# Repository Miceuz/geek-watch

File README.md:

# geek-watch
My take on building a watch.

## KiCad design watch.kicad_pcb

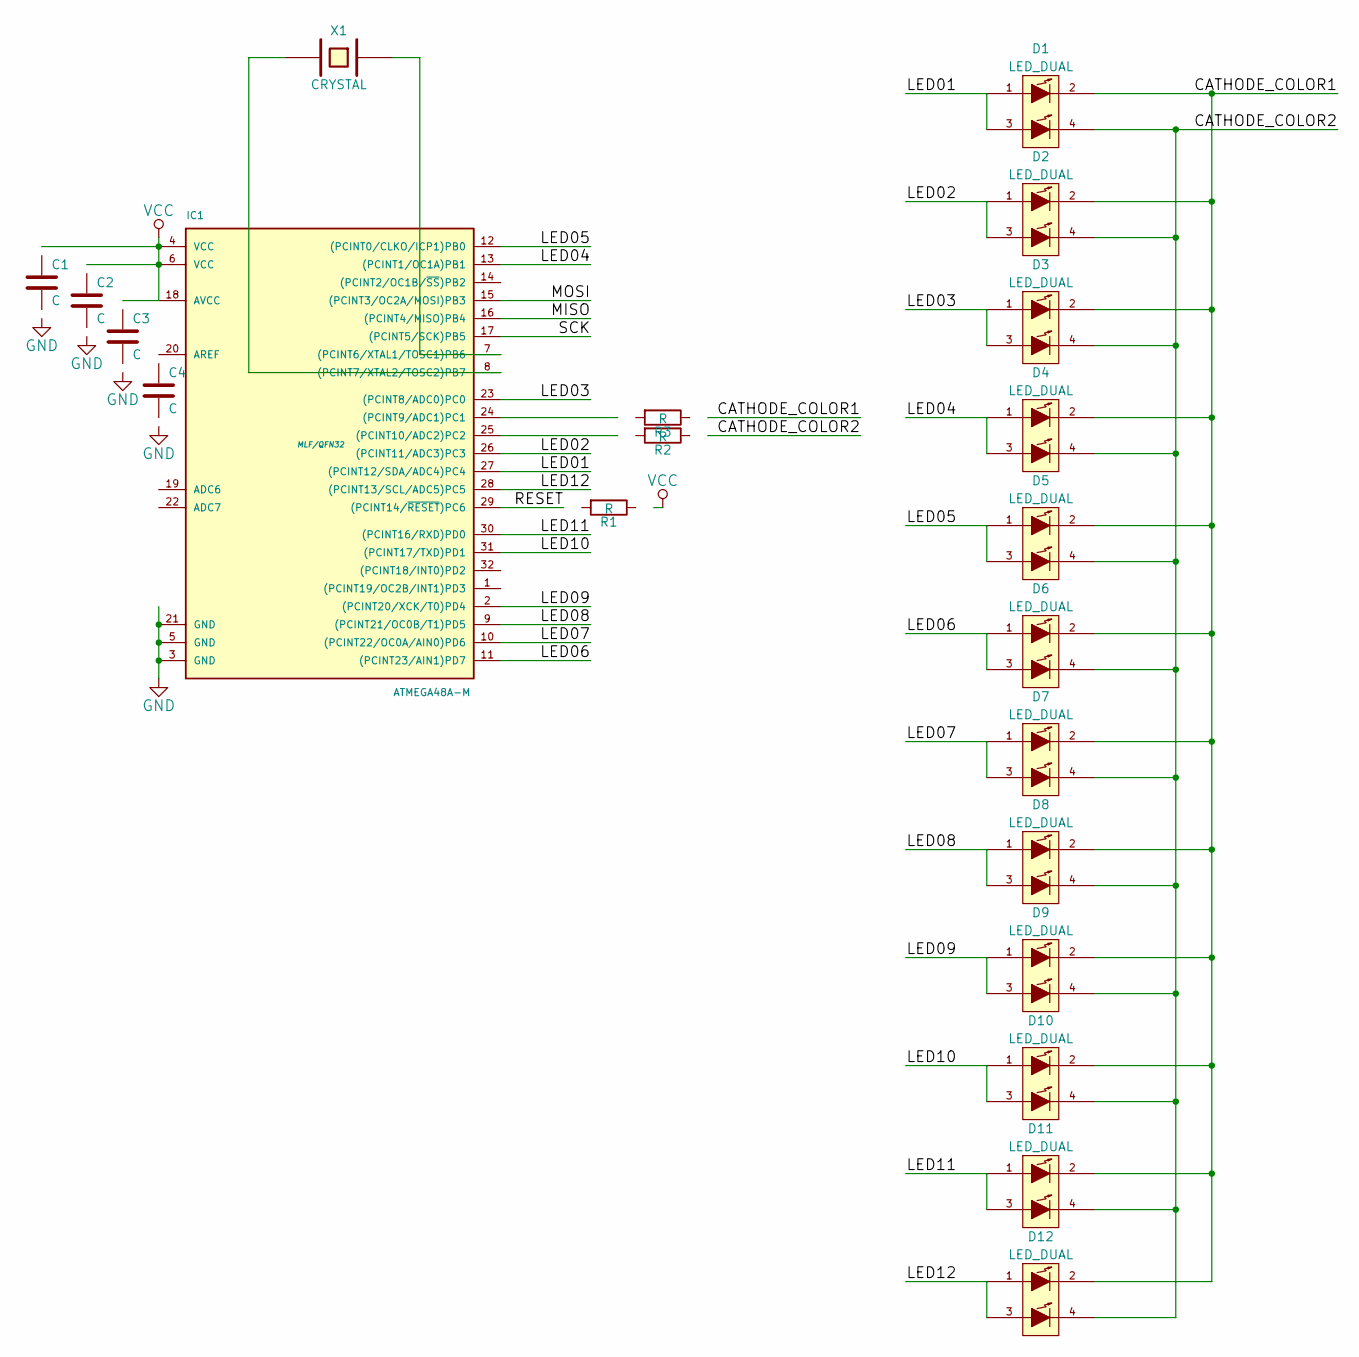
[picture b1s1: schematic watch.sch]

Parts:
C1, C2, C3, C4: C
D1, D2, D3, D4, D5, D6, D7, D8, D9, D10, D11, D12: LED_DUAL
IC1: ATMEGA48A-M; MLF/QFN32
R1, R2, R3: R
X1: CRYSTAL

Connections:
/CATHODE_COLOR1: D1.2 (RED_CATHODE), D2.2 (RED_CATHODE), D3.2 (RED_CATHODE), D4.2 (RED_CATHODE), D5.2 (RED_CATHODE), D6.2 (RED_CATHODE), D7.2 (RED_CATHODE), D8.2 (RED_CATHODE), D9.2 (RED_CATHODE), D10.2 (RED_CATHODE), D11.2 (RED_CATHODE), D12.2 (RED_CATHODE), R3.1
/CATHODE_COLOR2: D1.4 (GREEN_CATHODE), D2.4 (GREEN_CATHODE), D3.4 (GREEN_CATHODE), D4.4 (GREEN_CATHODE), D5.4 (GREEN_CATHODE), D6.4 (GREEN_CATHODE), D7.4 (GREEN_CATHODE), D8.4 (GREEN_CATHODE), D9.4 (GREEN_CATHODE), D10.4 (GREEN_CATHODE), D11.4 (GREEN_CATHODE), D12.4 (GREEN_CATHODE), R2.1
/LED01: D1.1 (RED_ANODE), D1.3 (GREEN_ANODE), IC1.27 ((PCINT12/SDA/ADC4)PC4)
/LED02: D2.1 (RED_ANODE), D2.3 (GREEN_ANODE), IC1.26 ((PCINT11/ADC3)PC3)
/LED03: D3.1 (RED_ANODE), D3.3 (GREEN_ANODE), IC1.23 ((PCINT8/ADC0)PC0)
/LED04: D4.1 (RED_ANODE), D4.3 (GREEN_ANODE), IC1.13 ((PCINT1/OC1A)PB1)
/LED05: D5.1 (RED_ANODE), D5.3 (GREEN_ANODE), IC1.12 ((PCINT0/CLKO/ICP1)PB0)
/LED06: D6.1 (RED_ANODE), D6.3 (GREEN_ANODE), IC1.11 ((PCINT23/AIN1)PD7)
/LED07: D7.1 (RED_ANODE), D7.3 (GREEN_ANODE), IC1.10 ((PCINT22/OC0A/AIN0)PD6)
/LED08: D8.1 (RED_ANODE), D8.3 (GREEN_ANODE), IC1.9 ((PCINT21/OC0B/T1)PD5)
/LED09: D9.1 (RED_ANODE), D9.3 (GREEN_ANODE), IC1.2 ((PCINT20/XCK/T0)PD4)
/LED10: D10.1 (RED_ANODE), D10.3 (GREEN_ANODE), IC1.31 ((PCINT17/TXD)PD1)
/LED11: D11.1 (RED_ANODE), D11.3 (GREEN_ANODE), IC1.30 ((PCINT16/RXD)PD0)
/LED12: D12.1 (RED_ANODE), D12.3 (GREEN_ANODE), IC1.28 ((PCINT13/SCL/ADC5)PC5)
/MISO: IC1.16 ((PCINT4/MISO)PB4); also elsewhere on the board
/MOSI: IC1.15 ((PCINT3/OC2A/MOSI)PB3); also elsewhere on the board
/RESET: IC1.29 ((PCINT14/~RESET~)PC6), R1.2; also elsewhere on the board
/SCK: IC1.17 ((PCINT5/SCK)PB5); also elsewhere on the board
GND: C1.2, C2.2, C3.2, IC1.3 (GND), IC1.5 (GND), IC1.21 (GND), IC1.33; also elsewhere on the board
unnamed: IC1.7 ((PCINT6/XTAL1/TOSC1)PB6), X1.1
unnamed: IC1.8 ((PCINT7/XTAL2/TOSC2)PB7), X1.2
unnamed: IC1.24 ((PCINT9/ADC1)PC1), R3.2
unnamed: IC1.25 ((PCINT10/ADC2)PC2), R2.2
VCC: C1.1, C2.1, C3.1, IC1.4 (VCC), IC1.6 (VCC), IC1.18 (AVCC), R1.1; also elsewhere on the board

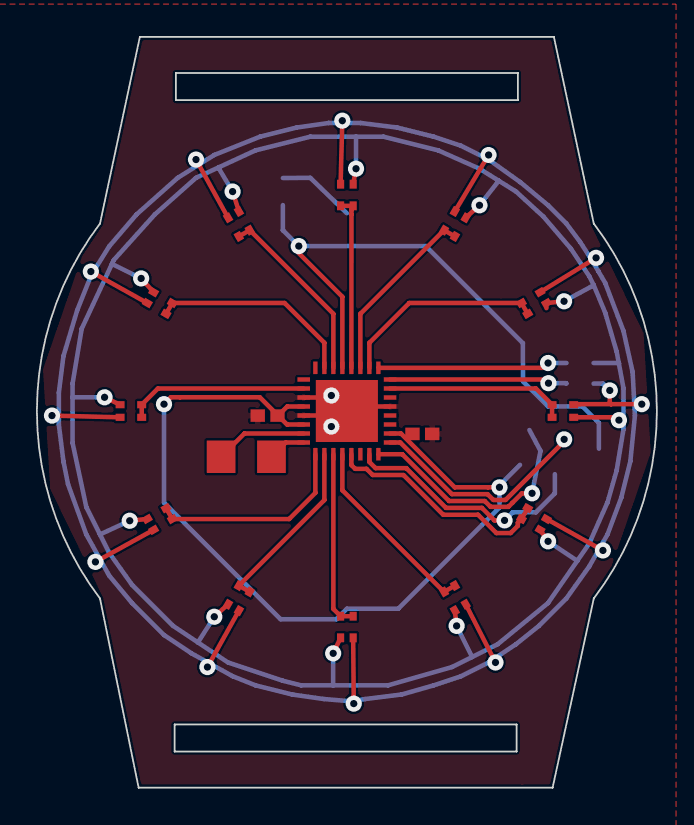
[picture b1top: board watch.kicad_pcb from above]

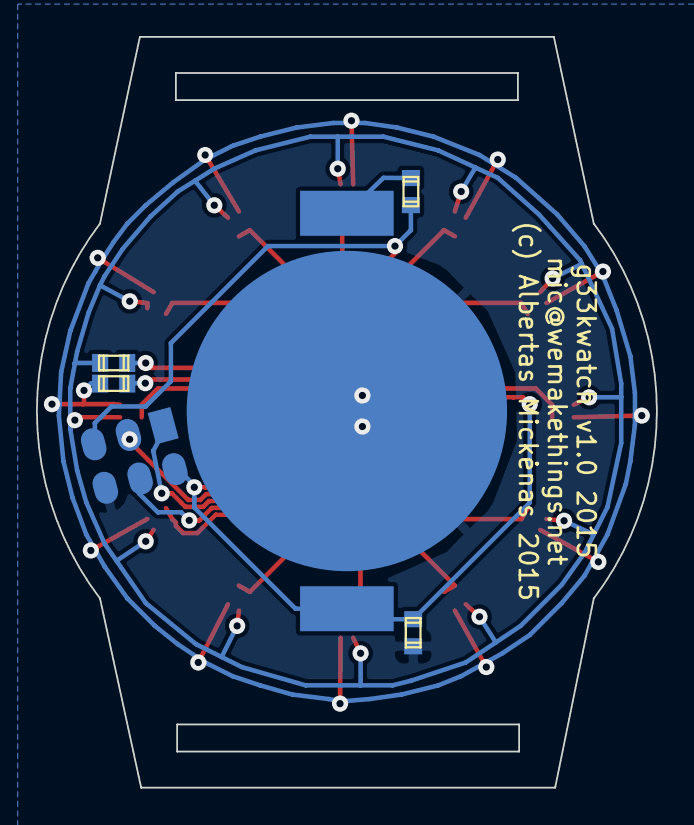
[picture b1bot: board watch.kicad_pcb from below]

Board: 2 copper layers, 34.4 x 41.7 mm, 22 parts (6 on the bottom side), 24 nets.

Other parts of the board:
BT1: BATTERY; BATT
PIN_SOCKET_2MM_3x2: Val**; pin_socket_2mm_3x2

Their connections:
/MISO: PIN_SOCKET_2MM_3x2.1; also elsewhere on the board
/MOSI: PIN_SOCKET_2MM_3x2.4; also elsewhere on the board
/RESET: PIN_SOCKET_2MM_3x2.5; also elsewhere on the board
/SCK: PIN_SOCKET_2MM_3x2.3; also elsewhere on the board
GND: BT1.1, PIN_SOCKET_2MM_3x2.6; also elsewhere on the board
VCC: BT1.2, PIN_SOCKET_2MM_3x2.2; also elsewhere on the board

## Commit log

2015-03-14 initial
2015-03-14 Add battery holder
2015-03-14 Correct pad numbers
2015-03-23 Are finished yet? I think we are...
2015-03-23 Add Y axis dimension
2015-03-25 Stupid kicad library update broke the schematics. Duhgit add .
2015-03-25 Cleanup silkscreen on top layer, change top footprints to 0402, add gerbers, send gerbers to pcb house.
